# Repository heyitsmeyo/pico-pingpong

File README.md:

# pico-pingpong

this is a python code to run a ping pong game on a raspberry pi pico with the circuitpython firmware installed in .....  

you need : 
   a raspberry pi pico ,
   breadboard ,
   buzzer ,
   arduino i2c display  , 

   first of all , download the circuitpython firmware from here :  
   
     https://circuitpython.org/

   then copy that file to the rpi drive 

copy also the required libraries like busio ....etc 

 you alos need an IDE  , download the thony ide from here : 

    https://thonny.org/

# PCB Design : 

# Schematic : 

# if you like the project , you can donate us for more : 

    https://ko-fi.com/heyitsmeyo

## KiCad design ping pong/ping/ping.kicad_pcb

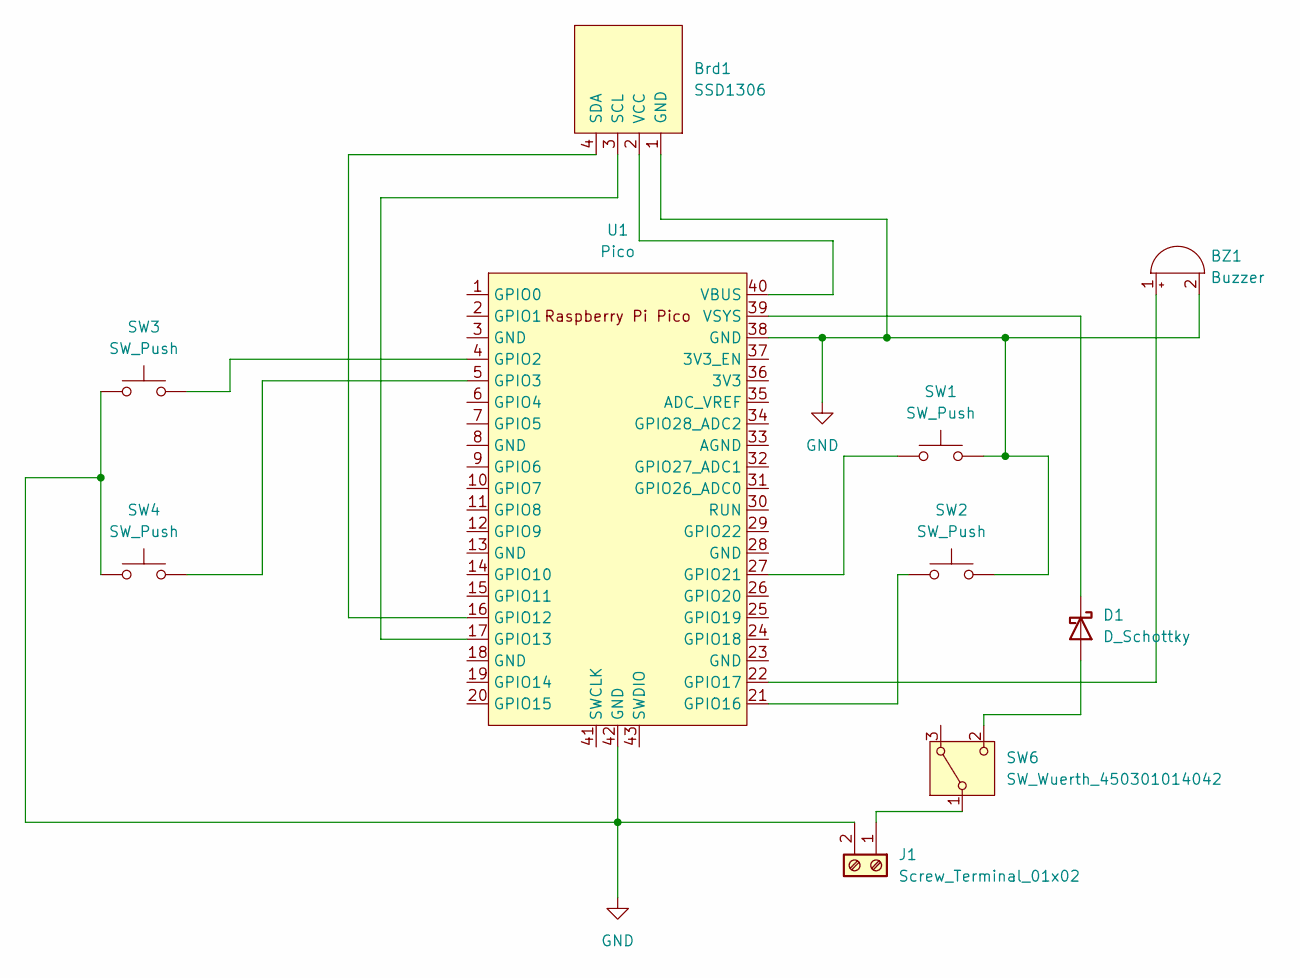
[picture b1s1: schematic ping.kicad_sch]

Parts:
BZ1: Buzzer; Buzzer_12x9.5RM7.6
Brd1: SSD1306; 128x64OLED
D1: D_Schottky; D_5W_P10.16mm_Horizontal
J1: Screw_Terminal_01x02; screwterminal
SW1, SW2, SW3, SW4: SW_Push; SW_PUSH_6mm_H4.3mm
SW6: SW_Wuerth_450301014042; SW_Slide-03_Wuerth-WS-SLTV_10x2.5x6.4_P2.54mm
U1: Pico; RPi_Pico_SMD_TH

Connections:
GND: BZ1.2 (-), Brd1.1 (GND), J1.2, SW1.2, SW2.2, SW3.1, SW4.1, U1.38 (GND), U1.42 (GND)
unnamed: BZ1.1 (+), U1.22 (GPIO17)
unnamed: Brd1.3 (SCL), U1.17 (GPIO13)
unnamed: Brd1.4 (SDA), U1.16 (GPIO12)
unnamed: Brd1.2 (VCC), U1.40 (VBUS)
unnamed: D1.2 (A), SW6.2 (C)
unnamed: D1.1 (K), U1.39 (VSYS)
unnamed: J1.1, SW6.1 (B)
unnamed: SW3.2, U1.4 (GPIO2)
unnamed: SW4.2, U1.5 (GPIO3)
unnamed: SW2.1, U1.21 (GPIO16)
unnamed: SW1.1, U1.27 (GPIO21)

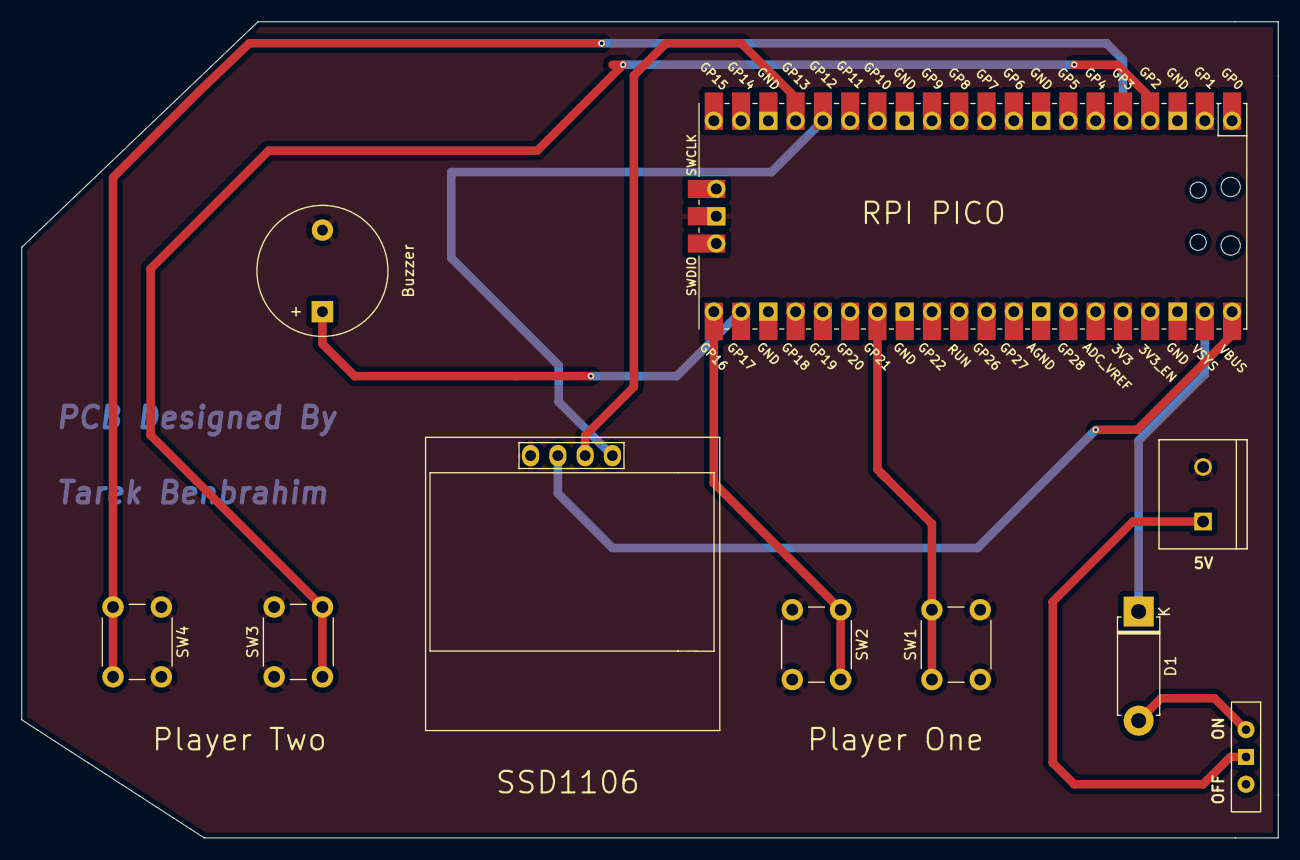
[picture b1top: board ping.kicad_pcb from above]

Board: 2 copper layers, 117.0 x 76.0 mm, 10 parts (0 on the bottom side), 12 nets.

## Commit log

2023-07-22 Add files via upload
    to run this code , you need to have a raspberry pi pico with circuitpyhton firmware installed in ....
